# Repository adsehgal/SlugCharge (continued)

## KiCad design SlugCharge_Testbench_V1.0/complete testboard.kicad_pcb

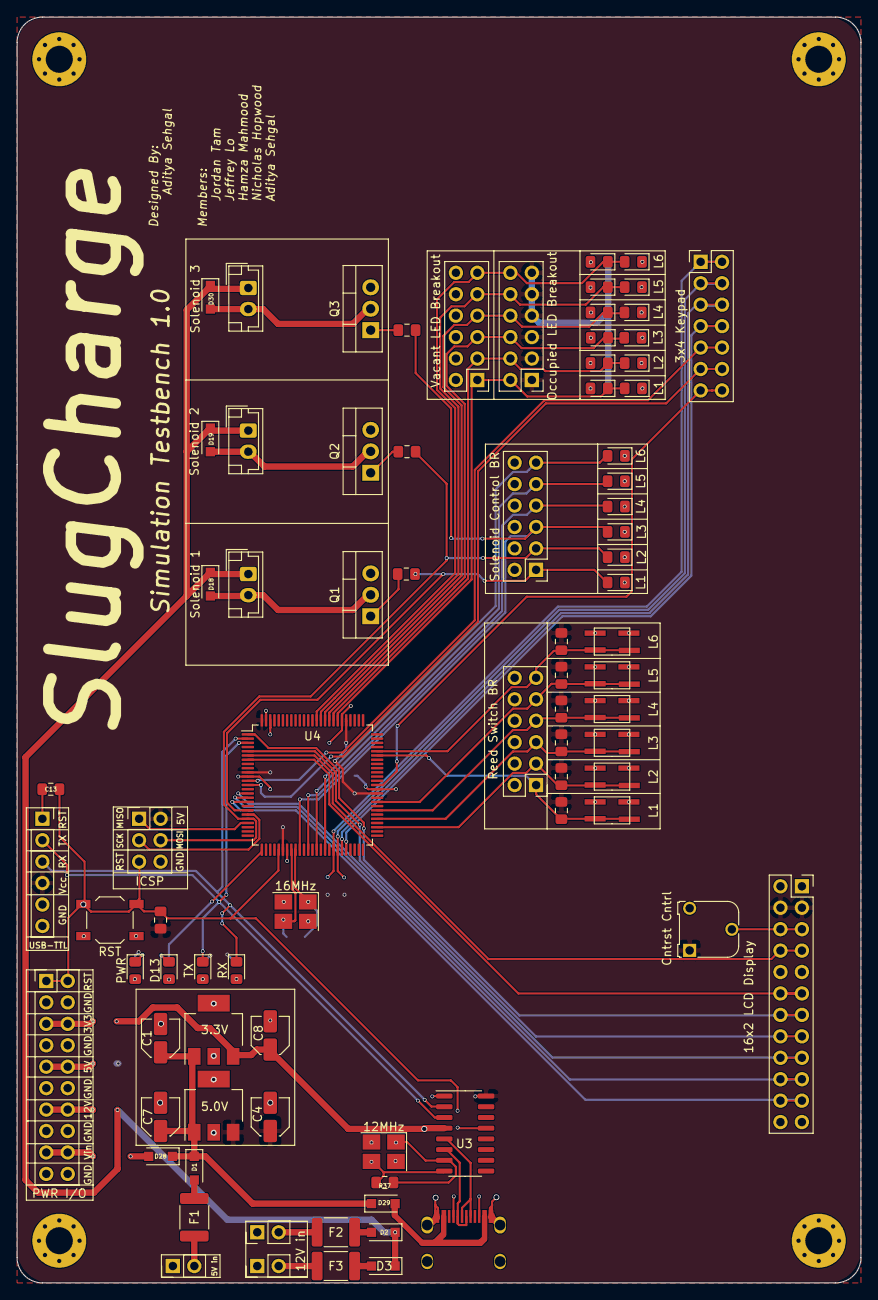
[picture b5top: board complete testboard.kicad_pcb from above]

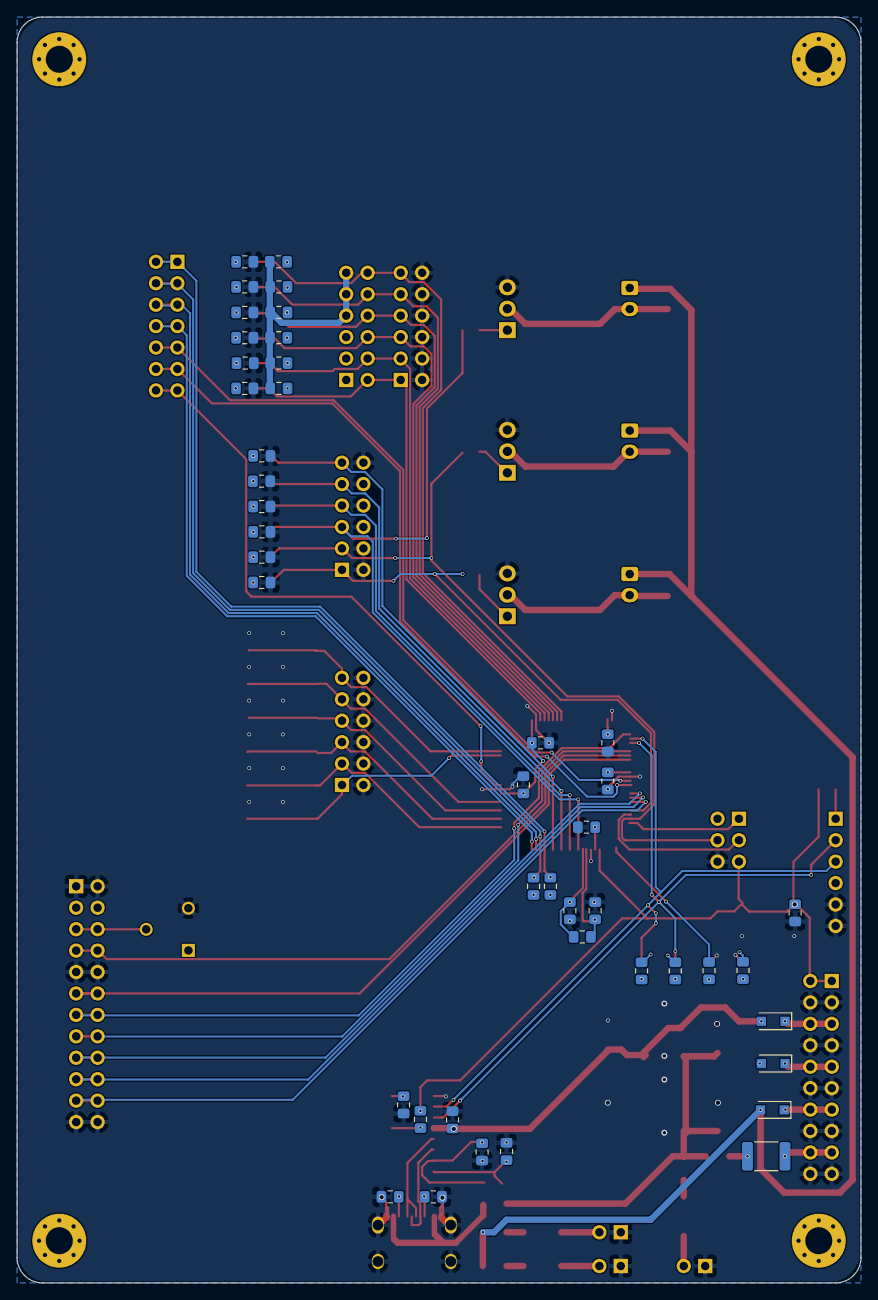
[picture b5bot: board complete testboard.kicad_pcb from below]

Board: 2 copper layers, 100.0 x 150.0 mm, 130 parts (44 on the bottom side), 95 nets.

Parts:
C1, C4, C7, C8: 10µF; C_Elec_4x5.4
C2, C3, C5, C6, C12, C13, C14, C15, C16: 100nF; C_0805_2012Metric_Pad1.15x1.40mm_HandSolder
C9, C10, C11, C17, C18: 22pF; C_0805_2012Metric_Pad1.15x1.40mm_HandSolder
D1, D2, D3, D25, D26, D27, D28, D29: D; D_SOD-123F
D4, D6, D17: L1; LED_0805_2012Metric_Pad1.15x1.40mm_HandSolder
D5, D8, D20: L2; LED_0805_2012Metric_Pad1.15x1.40mm_HandSolder
D7, D9, D21: L3; LED_0805_2012Metric_Pad1.15x1.40mm_HandSolder
D10, D12, D22: L4; LED_0805_2012Metric_Pad1.15x1.40mm_HandSolder
D11, D15, D23: L5; LED_0805_2012Metric_Pad1.15x1.40mm_HandSolder
D13: D13; LED_0805_2012Metric_Pad1.15x1.40mm_HandSolder
D14, D16, D24: L6; LED_0805_2012Metric_Pad1.15x1.40mm_HandSolder
D18, D19, D30: 1N4004; D_SOD-123F
F1, F2, F3, F4: Fuse; Fuse_1812_4532Metric_Pad1.30x3.40mm_HandSolder
H1, H2, H3, H4: MountingHole; MountingHole_3.2mm_M3_Pad_Via
J4: 5V in; PinHeader_1x02_P2.54mm_Vertical
J6, J7: 12V in; PinHeader_1x02_P2.54mm_Vertical
J8: Solenoid Control BR; PinHeader_2x06_P2.54mm_Vertical
J9: Vacant LED Breakout; PinHeader_2x06_P2.54mm_Vertical
J10: USB-TTL; PinSocket_1x06_P2.54mm_Vertical
J11: Occupied LED Breakout; PinHeader_2x06_P2.54mm_Vertical
J12: PWR I/O; PinHeader_2x10_P2.54mm_Vertical
J13: 16x2 LCD Display; PinSocket_2x12_P2.54mm_Vertical
J14: 3x4 Keypad; PinHeader_2x07_P2.54mm_Vertical
J15: Reed Switch BR; PinHeader_2x06_P2.54mm_Vertical
J16: ICSP; PinHeader_2x03_P2.54mm_Vertical
L1: Solenoid 1; JST_EH_B2B-EH-A_1x02_P2.50mm_Vertical
L2: Solenoid 2; JST_EH_B2B-EH-A_1x02_P2.50mm_Vertical
L3: Solenoid 3; JST_EH_B2B-EH-A_1x02_P2.50mm_Vertical
P1: USB_C_Plug; USB C C167321
PWR1: PWR; LED_0805_2012Metric_Pad1.15x1.40mm_HandSolder
Q1, Q2, Q3: TIP102; TO-220-3_Vertical
R1, R7, R8, R27, R28, R38: 1KΩ; R_0805_2012Metric_Pad1.15x1.40mm_HandSolder
R2, R37: 1MΩ; R_0805_2012Metric_Pad1.15x1.40mm_HandSolder
R3, R6: 5K1; R_0805_2012Metric_Pad1.15x1.40mm_HandSolder
R4, R5, R9, R10, R11, R12, R13, R14, R15, R16, R17, R18, R19, R20, R21, R22, R23, R24, R25, R26, R29, R30: 330Ω; R_0805_2012Metric_Pad1.15x1.40mm_HandSolder
R31, R32, R33, R34, R35, R36: 10KΩ; R_0805_2012Metric_Pad1.15x1.40mm_HandSolder
RV1: Cntrst Cntrl; Potentiometer_Runtron_RM-065_Vertical
RX1: RX; LED_0805_2012Metric_Pad1.15x1.40mm_HandSolder
SW1: RST; SW_SPST_TL3342
SW2: L1; PTS810_4.2x3.2
SW3: L2; PTS810_4.2x3.2
SW4: L3; PTS810_4.2x3.2
SW5: L4; PTS810_4.2x3.2
SW6: L5; PTS810_4.2x3.2
SW7: L6; PTS810_4.2x3.2
TX1: TX; LED_0805_2012Metric_Pad1.15x1.40mm_HandSolder
U1: 5.0V; SOT-223-3_TabPin2
U2: 3.3V; SOT-223-3_TabPin2
U3: CH340G; SOIC-16_3.9x9.9mm_P1.27mm
U4: ATmega2560-16AU; TQFP-100_14x14mm_P0.5mm
Y1: 16MHz; Crystal_SMD_3225-4Pin_3.2x2.5mm_HandSoldering
Y2: 12MHz; Crystal_SMD_3225-4Pin_3.2x2.5mm_HandSoldering

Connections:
+3V3: C8.1, C14.2, D25.2, U2.3, U3.4
+5V: C2.2, C3.2, C4.1, C5.2, C6.2, C15.2, D26.2, J10.4, J11.1, J11.3, J11.5, J11.7, J11.9, J11.11, J13.3, J13.4, J16.2, R1.2, R4.2, R7.2, R8.2, R9.2, R10.2, R23.2, R24.2, R25.2, R26.2, R29.2, R30.2, R31.2, R32.2, R33.2, R34.2, R35.2, R36.2, RV1.1, U1.3, U3.16, U4.10, U4.31, U4.61, U4.80, U4.100
+12V: D2.1, D3.1, D18.1, D19.1, D27.2, D30.1, L1.1, L2.1, L3.1
+VSW: C1.1, C7.1, D1.1, D28.1, D29.1, U1.1, U2.1
A10: D16.2, D24.1, J9.11, J11.12, U4.87
A11: D15.2, D23.1, J9.9, J11.10, U4.86
A12: D12.2, D22.1, J9.7, J11.8, U4.85
A13: D9.2, D21.1, J9.5, J11.6, U4.84
A14: D8.2, D20.1, J9.3, J11.4, U4.83
A15: D6.2, D17.1, J9.1, J11.2, U4.82
AREF: C12.1, U4.98
D0: J10.3, RX1.1, U3.2, U4.2
D1: J10.2, TX1.1, U3.3, U4.3
D2: J13.7, J13.8, U4.6
D3: J13.11, J13.12, U4.7
D4: J13.13, J13.14, U4.1
D5: J13.15, J13.16, U4.5
D6: J13.17, J13.18, U4.15
D7: J13.19, J13.20, U4.16
D8: J13.21, J13.22, U4.17
D13: R5.2, U4.26
D15: J14.13, J14.14, U4.63
D16: J14.11, J14.12, U4.13
D17: J14.9, J14.10, U4.12
D18: J14.7, J14.8, U4.46
D19: J14.5, J14.6, U4.45
D20: J14.3, J14.4, R8.1, U4.44
D21: J14.1, J14.2, R7.1, U4.43
D29: J15.11, R36.1, SW7.1, U4.71
D31: J15.9, R35.1, SW6.1, U4.59
D33: J15.7, R34.1, SW5.1, U4.57
D35: J15.5, R33.1, SW4.1, U4.55
D37: J15.3, R32.1, SW3.1, U4.53
D39: J15.1, R31.1, SW2.1, U4.70
D43: D14.2, J8.11, U4.41
D45: D11.2, J8.9, U4.39
D47: D10.2, J8.7, U4.37
D49: D7.2, J8.5, R38.1, U4.35
D50_MISO: J16.1, U4.22
D51_MOSI: D5.2, J8.3, J16.4, R28.1, U4.21
D52_SCK: J16.3, U4.20
D53_SS: D4.2, J8.1, R27.1, U4.19
D+: P1.A6, P1.B6, U3.5
D-: P1.A7, P1.B7, U3.6
GNDREF: C1.2, C2.1, C3.1, C4.2, C5.1, C6.1, C7.2, C8.2, C9.2, C10.2, C11.2, C12.2, C14.1, C15.1, C17.2, C18.2, D13.1, J4.1, J6.1, J7.1, J8.2, J8.4, J8.6, J8.8, J8.10, J8.12, J9.2, J9.4, J9.6, J9.8, J9.10, J9.12, J10.5, J10.6, J12.3, J12.4, J12.7, J12.8, J12.11, J12.12, J12.15, J12.16, J12.19, J12.20, J13.1, J13.2, J13.9, J13.10, J13.23, J13.24, J15.2, J15.4, J15.6, J15.8, J15.10, J15.12, J16.6, P1.A1, P1.A12, P1.B1, P1.B12, P1.S1, PWR1.1, Q1.3, Q2.3, Q3.3, R3.2, R6.2, R11.2, R12.2, R13.2, R14.2, R15.2, R16.2, R17.2, R18.2, R19.2, R20.2, R21.2, R22.2, RV1.3, SW1.2, SW2.2, SW3.2, SW4.2, SW5.2, SW6.2, SW7.2, U1.2, U2.2, U3.1, U4.11, U4.32, U4.62, U4.81, U4.99, Y1.2, Y1.4, Y2.2, Y2.4
unnamed: C9.1, R2.2, U4.34, Y1.1
unnamed: C10.1, R2.1, U4.33, Y1.3
unnamed: C13.2, J10.1
unnamed: C16.2, U3.13
unnamed: C17.1, R37.2, U3.7, Y2.1
unnamed: C18.1, R37.1, U3.8, Y2.3
unnamed: D1.2, F1.2
unnamed: D2.2, F2.2
unnamed: D3.2, F3.2
unnamed: D4.1, R11.1
unnamed: D5.1, R12.1
unnamed: D6.1, R13.1
unnamed: D7.1, R14.1
unnamed: D8.1, R15.1
unnamed: D9.1, R16.1
unnamed: D10.1, R17.1
unnamed: D11.1, R18.1
unnamed: D12.1, R19.1
unnamed: D13.2, R5.1
unnamed: D14.1, R20.1
unnamed: D15.1, R21.1
unnamed: D16.1, R22.1
unnamed: D17.2, R23.1
unnamed: D18.2, L1.2, Q1.2
unnamed: D19.2, L2.2, Q2.2
unnamed: D20.2, R24.1
unnamed: D21.2, R25.1
unnamed: D22.2, R26.1
unnamed: D23.2, R29.1
unnamed: D24.2, R30.1
unnamed: D25.1, J12.5, J12.6
unnamed: D26.1, J12.9, J12.10
unnamed: D27.1, J12.13, J12.14
unnamed: D28.2, F4.2
unnamed: D29.2, P1.A4, P1.A9, P1.B4, P1.B9
unnamed: D30.2, L3.2, Q3.2
unnamed: F1.1, J4.2
unnamed: F2.1, J6.2
unnamed: F3.1, J7.2
unnamed: F4.1, J12.17, J12.18
unnamed: J13.5, J13.6, RV1.2
unnamed: P1.A5, R3.1
unnamed: P1.B5, R6.1
unnamed: PWR1.2, R4.1
unnamed: Q1.1, R27.2
unnamed: Q2.1, R28.2
unnamed: Q3.1, R38.2
unnamed: R9.1, TX1.2
unnamed: R10.1, RX1.2
RST: C11.1, C13.1, C16.1, J12.1, J12.2, J16.5, R1.1, SW1.1, U4.30

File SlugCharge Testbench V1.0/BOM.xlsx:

Reference | Quantity | Value | KiCad Footprint | Standard Footprint | Datasheet | Purpose
C1 C4 C8 C7 | 4 | 10µF | Capacitor_SMD:C_Elec_4x5.4 | 4x5.4 SMD Cap | https://datasheet.lcsc.com/szlcsc/1810171406_ST-Semtech-CS1A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 | Voltage Regulation
C10 C9 C11 C18 C17 | 5 | 22pF | Capacitor_SMD:C_0805_2012Metric_Pad1.15x1.40mm_HandSolder | 0805 | https://datasheet.lcsc.com/szlcsc/1912111437_CCTC-TCC0805COG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 | Crystal
C5 C3 C2 C6 C12 C13 C14 C15 C16 | 9 | 100nF | Capacitor_SMD:C_0805_2012Metric_Pad1.15x1.40mm_HandSolder | 0805 | https://datasheet.lcsc.com/szlcsc/1811061718_FH-Guangdong-Fe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 | Voltage Regulation
D12 D22 D10 | 3 | L4 | LED_SMD:LED_0805_2012Metric_Pad1.15x1.40mm_HandSolder | 0805 | https://datasheet.lcsc.com/szlcsc/1811061716_Lite-On-LTST-C1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 | Locker Status
D13 | 1 | D13 | LED_SMD:LED_0805_2012Metric_Pad1.15x1.40mm_HandSolder | 0805 | https://datasheet.lcsc.com/szlcsc/1811061716_Lite-On-LTST-C1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 | System Status
D15 D23 D11 | 3 | L5 | LED_SMD:LED_0805_2012Metric_Pad1.15x1.40mm_HandSolder | 0805 | https://datasheet.lcsc.com/szlcsc/1811061716_Lite-On-LTST-C1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 | Locker Status
D16 D24 D14 | 3 | L6 | LED_SMD:LED_0805_2012Metric_Pad1.15x1.40mm_HandSolder | 0805 | https://datasheet.lcsc.com/szlcsc/1811061716_Lite-On-LTST-C1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 | Locker Status
D19 D18 D30 | 3 | 1N4004 | Diode_SMD:D_SOD-123F | SOD-123F | https://datasheet.lcsc.com/szlcsc/1810241423_Shandong-Jingda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 | Flyback Diode
D2 D1 D26 D25 D28 D27 D3 D29 | 8 | D | Diode_SMD:D_SOD-123F | SOD-123F | https://datasheet.lcsc.com/szlcsc/1810241423_Shandong-Jingda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 | Reverse Voltage Protection
D6 D17 D4 | 3 | L1 | LED_SMD:LED_0805_2012Metric_Pad1.15x1.40mm_HandSolder | 0805 | https://datasheet.lcsc.com/szlcsc/1811061716_Lite-On-LTST-C1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 | Locker Status
D8 D20 D5 | 3 | L2 | LED_SMD:LED_0805_2012Metric_Pad1.15x1.40mm_HandSolder | 0805 | https://datasheet.lcsc.com/szlcsc/1811061716_Lite-On-LTST-C1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 | Locker Status
D9 D21 D7 | 3 | L3 | LED_SMD:LED_0805_2012Metric_Pad1.15x1.40mm_HandSolder | 0805 | https://datasheet.lcsc.com/szlcsc/1811061716_Lite-On-LTST-C1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 | Locker Status
F2 F1 F4 F3 | 4 | Fuse | Fuse:Fuse_1812_4532Metric_Pad1.30x3.40mm_HandSolder | 1812 | https://datasheet.lcsc.com/szlcsc/1912111437_Jinrui-Electron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 | Over Voltage Protection
H1 H2 H3 H4 | 4 | MountingHole | MountingHole:MountingHole_3.2mm_M3_Pad_Via | M3 | N/A | Mounting
HS2 HS1 HS3 | 3 | Heatsink | Heatsink:TO-220 Vertical XSD C116600 | T0-220 HS | https://datasheet.lcsc.com/szlcsc/1810010332_XSD-C116600_C11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 | Thermal Protection
J10 | 1 | USB-TTL | Connector_PinSocket_2.54mm:PinSocket_1x06_P2.54mm_Vertical | 1x6 2.54mm | N/A | Programming
J11 | 1 | Occupied LED Breakout | Connector_PinHeader_2.54mm:PinHeader_2x06_P2.54mm_Vertical | 2x6 2.54mm | N/A | Locker Status
J12 | 1 | PWR I/O | Connector_PinHeader_2.54mm:PinHeader_2x10_P2.54mm_Vertical | 2x10 2.54mm | N/A | Power
J13 | 1 | 16x2 LCD Display | Connector_PinSocket_2.54mm:PinSocket_2x12_P2.54mm_Vertical | 2x12 2.54mm | N/A | LCD
J14 | 1 | 3x4 Keypad | Connector_PinHeader_2.54mm:PinHeader_2x07_P2.54mm_Vertical | 2x7 2.54mm | N/A | Keypad
J15 | 1 | Reed Switch BR | Connector_PinHeader_2.54mm:PinHeader_2x06_P2.54mm_Vertical | 2x6 2.54mm | N/A | Reed Switch
J16 | 1 | ICSP | Connector_PinHeader_2.54mm:PinHeader_2x03_P2.54mm_Vertical | 2x3 2.54mm | N/A | Programming
J4 | 1 | 5V in | Connector_PinHeader_2.54mm:PinHeader_1x02_P2.54mm_Vertical | 1x2 2.54mm | N/A | Power
J6 J7 | 2 | 12V in | Connector_PinHeader_2.54mm:PinHeader_1x02_P2.54mm_Vertical | 1x2 2.54mm | N/A | Power
J8 | 1 | Solenoid Control Breakout | Connector_PinHeader_2.54mm:PinHeader_2x06_P2.54mm_Vertical | 2x6 2.54mm | N/A | Solenoid
J9 | 1 | Vacant LED Breakout | Connector_PinHeader_2.54mm:PinHeader_2x06_P2.54mm_Vertical | 2x6 2.54mm | N/A | Locker Status
L1 | 1 | Solenoid 1 | Connector_JST:JST_EH_B2B-EH-A_1x02_P2.50mm_Vertical | 2.5mm JST | https://datasheet.lcsc.com/szlcsc/1810291311_JST-Sales-Ameri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 | Solenoid
L2 | 1 | Solenoid 2 | Connector_JST:JST_EH_B2B-EH-A_1x02_P2.50mm_Vertical | 2.5mm JST | https://datasheet.lcsc.com/szlcsc/1810291311_JST-Sales-Ameri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 | Solenoid
L3 | 1 | Solenoid 3 | Connector_JST:JST_EH_B2B-EH-A_1x02_P2.50mm_Vertical | 2.5mm JST | https://datasheet.lcsc.com/szlcsc/1810291311_JST-Sales-Ameri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 | Solenoid
P1 | 1 | USB_C_Plug | Connector_USB:USB C C167321 | USB C C167321 | https://datasheet.lcsc.com/szlcsc/1811101520_Jing-Extension-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 | Programming
PWR1 | 1 | PWR | LED_SMD:LED_0805_2012Metric_Pad1.15x1.40mm_HandSolder | 0805 | https://datasheet.lcsc.com/szlcsc/1811061716_Lite-On-LTST-C1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 | System Status
Q2 Q1 Q3 | 3 | TIP102 | Package_TO_SOT_THT:TO-220-3_Vertical | T0-220 | www.irf.com/product-info/datasheets/data/irf540n.pdf | Solenoid Control
R2 R37 | 2 | 1MΩ | Resistor_SMD:R_0805_2012Metric_Pad1.15x1.40mm_HandSolder | 0805 | https://datasheet.lcsc.com/szlcsc/1811061718_FH-Guangdong-Fe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 | Crystal Isolator
R3 R6 | 2 | 5.1KΩ | Resistor_SMD:R_0805_2012Metric_Pad1.15x1.40mm_HandSolder | 0805 | https://datasheet.lcsc.com/szlcsc/1811061718_FH-Guangdong-Fe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 | USB CC
R31 R32 R33 R34 R35 R36 | 6 | 10KΩ | Resistor_SMD:R_0805_2012Metric_Pad1.15x1.40mm_HandSolder | 0805 | https://datasheet.lcsc.com/szlcsc/1811061718_FH-Guangdong-Fe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 | Current Limiting
R4 R5 R9 R10 R13 R15 R16 R19 R21 R22 R23 R24 R25 R26 R29 R30 R11 R12 R14 R17 R1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 | 22 | 330Ω | Resistor_SMD:R_0805_2012Metric_Pad1.15x1.40mm_HandSolder | 0805 | https://datasheet.lcsc.com/szlcsc/1811061718_FH-Guangdong-Fe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 | Current Limiting
R8 R7 R1 R28 R27 R38 | 6 | 1KΩ | Resistor_SMD:R_0805_2012Metric_Pad1.15x1.40mm_HandSolder | 0805 | https://datasheet.lcsc.com/szlcsc/1811061718_FH-Guangdong-Fe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 | Current Limiting
RV1 | 1 | 10KΩ | Potentiometer_THT:Potentiometer_Runtron_RM-065_Vertical | RM65 | https://www.amazon.com/gp/product/B00SWK15KE/ref=ppx_yo_dt_b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 | Contrast
RX1 | 1 | RX | LED_SMD:LED_0805_2012Metric_Pad1.15x1.40mm_HandSolder | 0805 | https://datasheet.lcsc.com/szlcsc/1811061718_FH-Guangdong-Fe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 | System Status
SW1 | 1 | RST | Button_Switch_SMD:SW_SPST_TL3342 | TL3342 | https://datasheet.lcsc.com/szlcsc/1811082127_Korean-Hroparts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 | System Reset
SW2 | 1 | L1 | Button_Switch_SMD:PTS810_4.2x3.2 | PTS810 | https://datasheet.lcsc.com/szlcsc/1811092141_C-K-PTS810SJM25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 | Door Simulation
SW3 | 1 | L2 | Button_Switch_SMD:PTS810_4.2x3.2 | PTS810 | https://datasheet.lcsc.com/szlcsc/1811092141_C-K-PTS810SJM25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 | Door Simulation
SW4 | 1 | L3 | Button_Switch_SMD:PTS810_4.2x3.2 | PTS810 | https://datasheet.lcsc.com/szlcsc/1811092141_C-K-PTS810SJM25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 | Door Simulation
SW5 | 1 | L4 | Button_Switch_SMD:PTS810_4.2x3.2 | PTS810 | https://datasheet.lcsc.com/szlcsc/1811092141_C-K-PTS810SJM25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 | Door Simulation
SW6 | 1 | L5 | Button_Switch_SMD:PTS810_4.2x3.2 | PTS810 | https://datasheet.lcsc.com/szlcsc/1811092141_C-K-PTS810SJM25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 | Door Simulation
SW7 | 1 | L6 | Button_Switch_SMD:PTS810_4.2x3.2 | PTS810 | https://datasheet.lcsc.com/szlcsc/1811092141_C-K-PTS810SJM25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 | Door Simulation
TX1 | 1 | TX | LED_SMD:LED_0805_2012Metric_Pad1.15x1.40mm_HandSolder | 0805 | https://datasheet.lcsc.com/szlcsc/1811061718_FH-Guangdong-Fe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 | System Status
U1 | 1 | ams1117-5.0V | Package_TO_SOT_SMD:SOT-223-3_TabPin2 | SOT-223 | https://datasheet.lcsc.com/szlcsc/1912111437_UMW-Youtai-Semi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 | Voltage Regulation
U2 | 1 | ams1117-3.3V | Package_TO_SOT_SMD:SOT-223-3_TabPin2 | SOT-223 | https://datasheet.lcsc.com/szlcsc/1912111437_UMW-Youtai-Semi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 | Voltage Regulation
U3 | 1 | CH340G | Package_SO:SOIC-16_3.9x9.9mm_P1.27mm | SOIC-16 | https://datasheet.lcsc.com/szlcsc/1811130504_WCH-Jiangsu-Qin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 | UART
U4 | 1 | ATmega2560-16AU | Package_QFP:TQFP-100_14x14mm_P0.5mm | TQFP-100 | www.microchip.com/downloads/en/DeviceDoc/Atmel-2549-8-bit-AVR-Microcontroller-A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 | µcontroller
Y1 | 1 | 16MHz | Crystal:Crystal_SMD_3225-4Pin_3.2x2.5mm_HandSoldering | 3225-4pin | https://datasheet.lcsc.com/szlcsc/1912111437_JGHC-S321600020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 | Clock
Y2 | 1 | 12MHz | Crystal:Crystal_SMD_3225-4Pin_3.2x2.5mm_HandSoldering | 3225-4pin | https://datasheet.lcsc.com/szlcsc/1912111437_JGHC-S321600020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 | Clock

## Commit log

2020-05-26 Pushed all final project files
2020-05-29 updated TPS62133
2020-06-05 added 3d drawings
2020-08-07 readme update
2020-08-07 readme init
2020-08-07 ReadMe in progress
2020-08-07 PDF try
2020-08-07 Convert schem PDF to png
2020-08-07 PCB #1 complete
2020-08-07 README PCB Section Complete
2020-08-07 Mech section complete - link needed
2020-08-07 README complete
2020-10-13 added final report
2020-10-13 pushed regulator seletion
